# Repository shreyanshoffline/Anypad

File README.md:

# The Anypad ♾️

A custom left-hand gaming macropad that *actually* respects your muscle memory. Built for the Hack Club Hackpad program.

Most macropads use a rigid ortholinear grid, which is terrible for gaming. If you try to play Minecraft, Fortnite, or Roblox on a square grid, your fingers get confused because normal keyboards have a staggered layout. 

**The Anypad** fixes this. It features a true QWERTY-accurate 0.25U stagger for the WASD movement cluster, a dedicated thumb spacebar, and stacked pinky keys for Shift/Ctrl. Add an OLED screen, a rotary encoder, and an aggressive amount of RGB, and you have the ultimate mini-pad designed to seamlessly swap between gaming, office, and study modes.

>[!CAUTION]
>Below will be very revoulutionary designs and technology that is game-changing, literally

## 📸 The Screenshots

These are some screenshots of the PCB, Schematic, Case, And Complete Build.

### Overall Hackpad

*(Note: Coming soon! After Build)*

### Schematic

### PCB Layout

>[!NOTE]
>Check out the silkscreen art

### CAD in Fusion360

---

## ✨ Features
* **Muscle-Memory Layout:** 9 mechanical switches arranged with realistic desktop stagger so you don't miss inputs mid-game or while locked in during work.
* **The Brain:** Powered by The Seeed Studio XIAO RP2040 Microcontroller. Small, But Mighty
* **The Screen:** A 0.91" OLED display to give visual feedback on your current active profile (Gaming 🎮 / Office 🏢 / Study ✏️).
* **The Knob** Instead of using keys to switch inventory slots, or raise and reduce volume the knob allows you to do more while taking less space.

## ✅ Benefits
* **Light, Small, Fast:** Instead of carrying an entire keyboard all you need is a mouse and The Anypad. Easily portable and gives you more desk space.
* **Focus, Study, Game:** Switch between focus modes in the swift turn of a knob. Quickly immerse your self in the gaming world or into optimized work and study shortcuts
* **RGB Everything:** 17 total SK6812 MINI-E addressable LEDs (9 per-key backlights + 8 corner underglows for a seamless desk halo effect). Instantly turns up your vibe
* **Ergonomics Over Symmetry:** The Anypad prioritizes hand comfort over artificial symmetry. While the layout might look like an unusual angle at first glance, it naturally aligns with where your fingers want to rest during long gaming sessions.

## </> Firmware Overview
The Anypad uses QMK for everything

>[!NOTE]
> Via will be added soon for instant flashing and customization

## 🧰 Bill of Materials (BOM)

| Component | Qty | Description |
| :--- | :---: | :--- |
| Seeed XIAO RP2040 | 1 | The Brains of the system, A Mighty little Microcontroller |
| EC11 Rotary Encoder | 1 | Rotating knob, with push-button functionality |
| Encoder Knob | 1 | Fits over the EC11 shaft |
| 0.91" OLED Display | 1 | Standard 4-pin breakout (GND, VCC, SCL, SDA) |
| Reverse Mount SK6812 MINI-E LEDs | 17 | 9 for Keys, 8 for bottom underglow |
| Through-Hole 1N4148 Diodes | 9 | For the 3x3 anti-ghosting matrix |
| Custom PCB (In /PCB)| 1 | Holds and connects all electrical components |
| Custom 3D Printed Case (In /Production)| 1 | Top plate + bottom enclosure |
| Blank White DSA Keycaps | 9 | 1U caps, Smooth and blank |
| MX-Style Keyswitches | 9 | The Nice Clicky Kind |
| M3x16mm screws | 4 | Tiny Screws That hold everything together |
| M3x5mx4mm Brass Heatset Inserts | 4 | Brass treads that makes the case re-openable |
>[!NOTE]
> You may also need a solder, soldering iron and other soldering accessories for completing the build

>[!TIP]
> You can get all the materials for free or bundled from the Hackpad Kit by Hack club. 

## 🧠 Behind the Hardware (The Wiring Matrix)

To make everything fit on the XIAO's extremely limited edge pins, the 9 keys are wired into a standard 3x3 diode matrix (using only 6 pins). 

This is a basic efficient layout that frees up the remaining pins perfectly for the OLED (2 pins), the Rotary Encoder (2 pins), and a single data line chained through all 17 LEDs without needing to resort to hidden pads or larger microcontrollers. 

---
> Designed by [shreyanshoffline](https://github.com/shreyanshoffline) for The Stardance Challenge by Hack Club, NASA, AMD, and Github.

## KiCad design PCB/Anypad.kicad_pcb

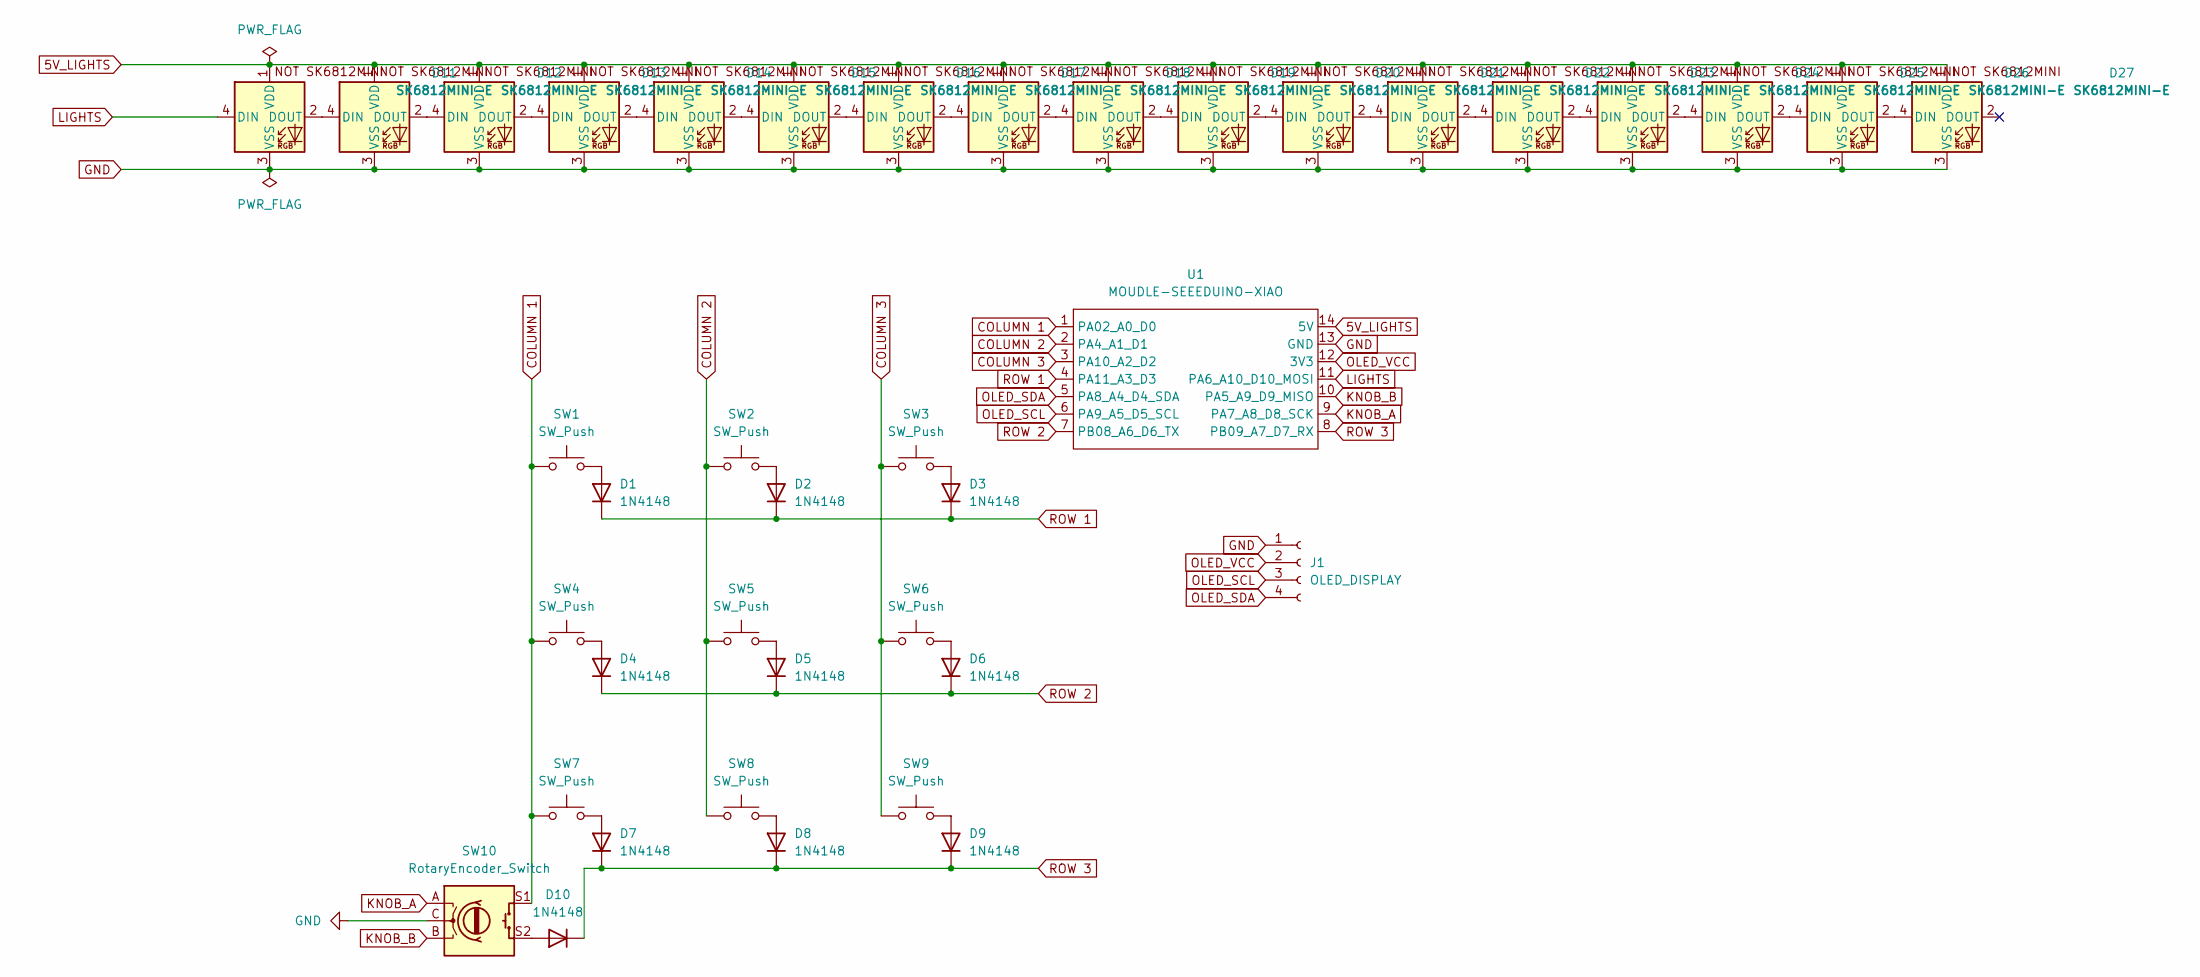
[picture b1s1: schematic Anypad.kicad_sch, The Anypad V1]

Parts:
D1, D2, D3, D4, D5, D6, D7, D8, D9, D10: 1N4148; D_DO-35_SOD27_P7.62mm_Horizontal
D11, D12, D13, D14, D15, D16, D17, D18, D19, D20, D21, D22, D23, D24, D25, D26, D27: SK6812MINI-E; SK6812MINI-E_fixed
J1: OLED_DISPLAY; SSD1306-0.91-OLED-4pin-128x32
SW1, SW2, SW3, SW4, SW5, SW6, SW7, SW8, SW9: SW_Push; SW_Cherry_MX_1.00u_PCB
SW10: RotaryEncoder_Switch; RotaryEncoder_Alps_EC11E-Switch_Vertical_H20mm
U1: MOUDLE-SEEEDUINO-XIAO; XIAO-Generic-Hybrid-14P-2.54-21X17.8MM

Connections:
5V_LIGHTS: D11.1 (VDD), D12.1 (VDD), D13.1 (VDD), D14.1 (VDD), D15.1 (VDD), D16.1 (VDD), D17.1 (VDD), D18.1 (VDD), D19.1 (VDD), D20.1 (VDD), D21.1 (VDD), D22.1 (VDD), D23.1 (VDD), D24.1 (VDD), D25.1 (VDD), D26.1 (VDD), D27.1 (VDD), U1.14 (5V)
COLUMN 1: SW1.1, SW4.1, SW7.1, SW10.S1, U1.1 (PA02_A0_D0)
COLUMN 2: SW2.1, SW5.1, SW8.1, U1.2 (PA4_A1_D1)
COLUMN 3: SW3.1, SW6.1, SW9.1, U1.3 (PA10_A2_D2)
GND: D11.3 (VSS), D12.3 (VSS), D13.3 (VSS), D14.3 (VSS), D15.3 (VSS), D16.3 (VSS), D17.3 (VSS), D18.3 (VSS), D19.3 (VSS), D20.3 (VSS), D21.3 (VSS), D22.3 (VSS), D23.3 (VSS), D24.3 (VSS), D25.3 (VSS), D26.3 (VSS), D27.3 (VSS), J1.1, SW10.C, U1.13 (GND)
KNOB_A: SW10.A, U1.9 (PA7_A8_D8_SCK)
KNOB_B: SW10.B, U1.10 (PA5_A9_D9_MISO)
LIGHTS: D11.4 (DIN), U1.11 (PA6_A10_D10_MOSI)
unnamed: D1.2 (A), SW1.2
unnamed: D2.2 (A), SW2.2
unnamed: D3.2 (A), SW3.2
unnamed: D4.2 (A), SW4.2
unnamed: D5.2 (A), SW5.2
unnamed: D6.2 (A), SW6.2
unnamed: D7.2 (A), SW7.2
unnamed: D8.2 (A), SW8.2
unnamed: D9.2 (A), SW9.2
unnamed: D10.2 (A), SW10.S2
unnamed: D11.2 (DOUT), D12.4 (DIN)
unnamed: D12.2 (DOUT), D13.4 (DIN)
unnamed: D13.2 (DOUT), D14.4 (DIN)
unnamed: D14.2 (DOUT), D15.4 (DIN)
unnamed: D15.2 (DOUT), D16.4 (DIN)
unnamed: D16.2 (DOUT), D17.4 (DIN)
unnamed: D17.2 (DOUT), D18.4 (DIN)
unnamed: D18.2 (DOUT), D19.4 (DIN)
unnamed: D19.2 (DOUT), D20.4 (DIN)
unnamed: D20.2 (DOUT), D21.4 (DIN)
unnamed: D21.2 (DOUT), D22.4 (DIN)
unnamed: D22.2 (DOUT), D23.4 (DIN)
unnamed: D23.2 (DOUT), D24.4 (DIN)
unnamed: D24.2 (DOUT), D25.4 (DIN)
unnamed: D25.2 (DOUT), D26.4 (DIN)
unnamed: D26.2 (DOUT), D27.4 (DIN)
OLED_SCL: J1.3, U1.6 (PA9_A5_D5_SCL)
OLED_SDA: J1.4, U1.5 (PA8_A4_D4_SDA)
OLED_VCC: J1.2, U1.12 (3V3)
ROW 1: D1.1 (K), D2.1 (K), D3.1 (K), U1.4 (PA11_A3_D3)
ROW 2: D4.1 (K), D5.1 (K), D6.1 (K), U1.7 (PB08_A6_D6_TX)
ROW 3: D7.1 (K), D8.1 (K), D9.1 (K), D10.1 (K), U1.8 (PB09_A7_D7_RX)

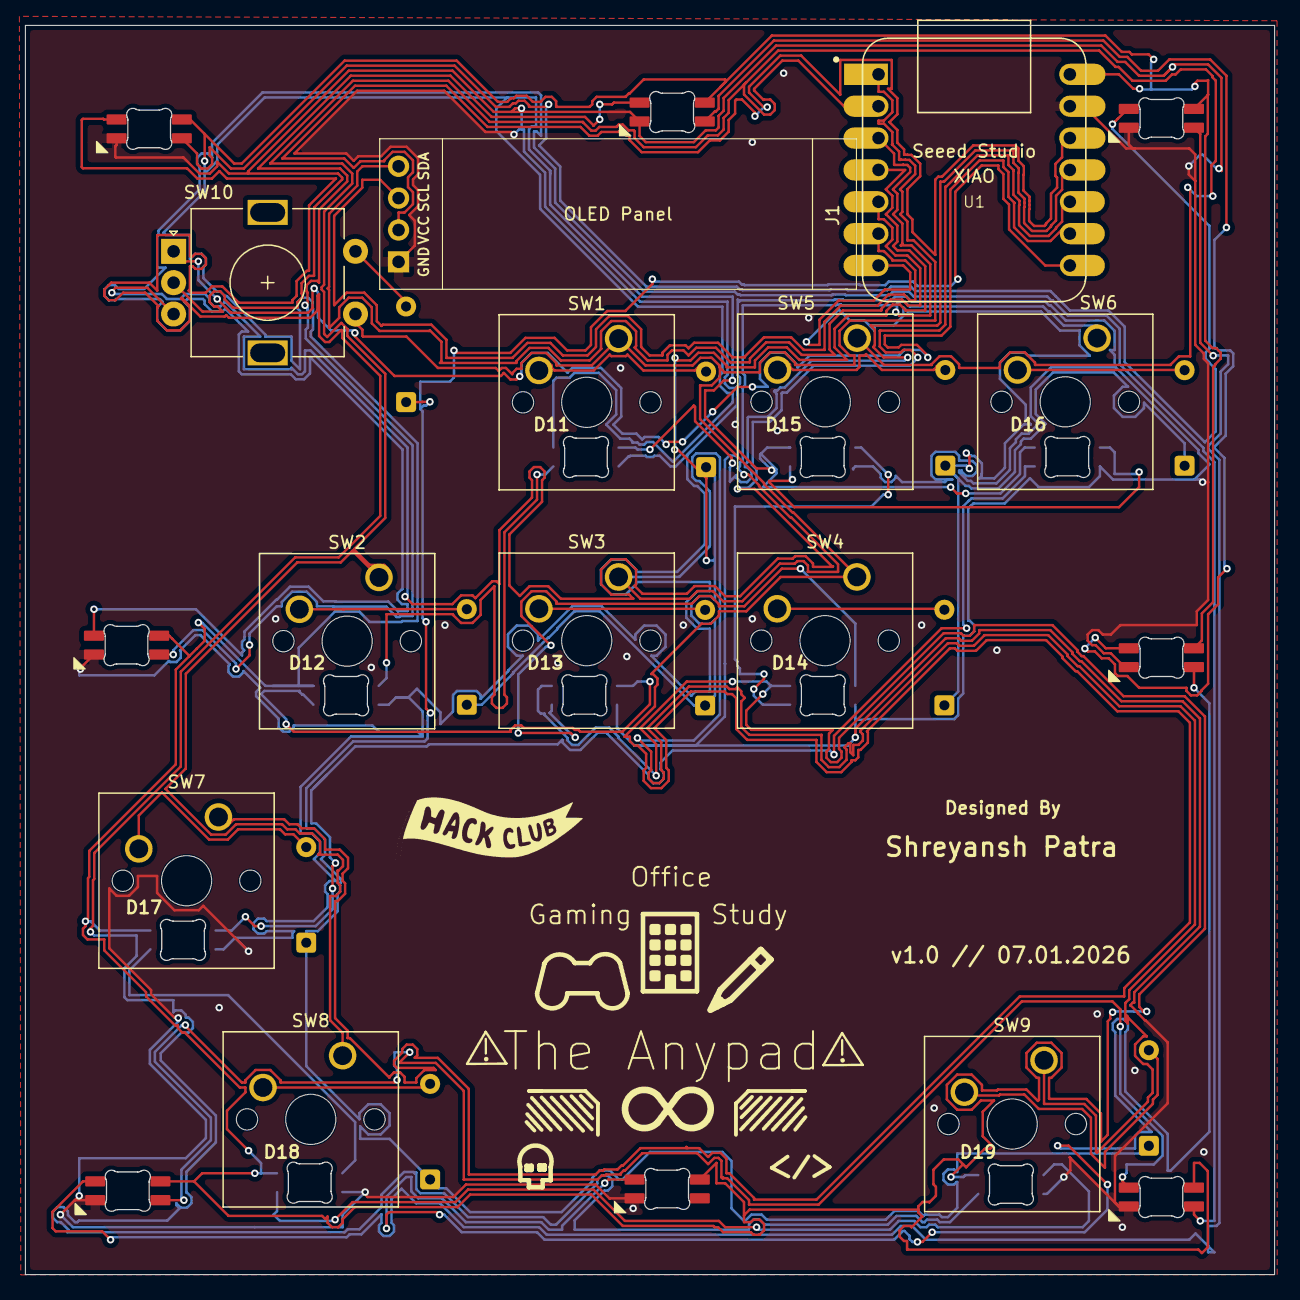
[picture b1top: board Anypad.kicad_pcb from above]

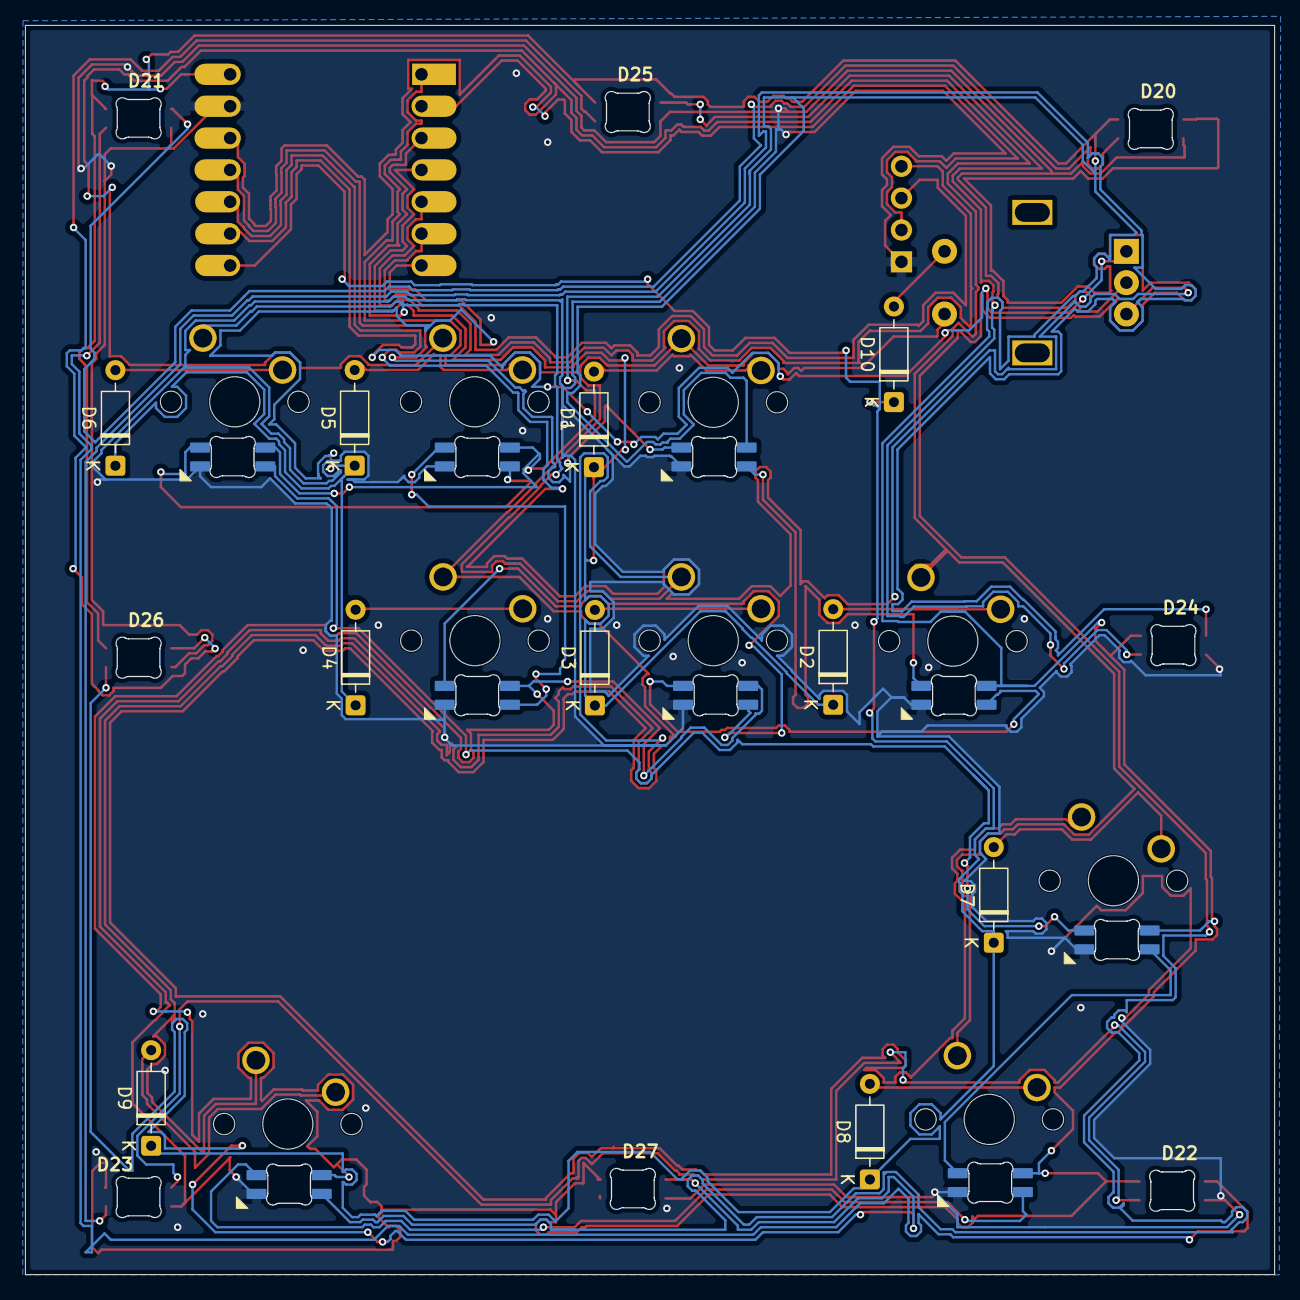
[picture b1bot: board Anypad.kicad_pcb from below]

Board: 2 copper layers, 99.5 x 99.5 mm, 39 parts (18 on the bottom side), 40 nets.

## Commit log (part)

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2026-06-22 Pcb files
2026-06-23 Folder Organization
2026-06-24 Initialize README with Anypad project details First Draft
    Added detailed description, features, and BOM for the Anypad.
